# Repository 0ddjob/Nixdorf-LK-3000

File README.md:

# Nixdorf LK-3000
Information about the Nixdorf LK-3000 personal computer.<br>

The cartridges use the Mostek MK3870 CPU and MK3600 ROM.  The CPU contains its own ROM and RAM which can be [dumped](https://github.com/blackjetrock/dumper_m3780) thanks to the existence of a TEST pin!<br>

## Videos
- [Part 1: first look & disassembly](https://youtu.be/9jknng2B5vs)
- [Part 2: let's start hacking it](https://youtu.be/iGiR7imZPvE)
- [Part 3: Hello World!](https://youtu.be/sHEaltcKjgI)

## [Arduino Code](/Arduino/Hello_World/Hello_World.ino)
The first new software written for the LK-3000 in 40 years?!  Some test code to see how it works - replaced the cartridge connector with a 16-way pin header for easy wiring up to an Arduino.<br>

Check also the [July 1980 issue of Popular Electronics](/Documentation/Poptronics_July_1980.pdf) that describes how to re-use the LK-3000.

## [Dumping the MK3870 firmware](https://hackaday.com/tag/mk3870/)

## [Schematic](/LK3000_Schematics)
A schematic (KiCad 9) of the LK-3000.  The machine is essentially just a keyboard & display with the cartridges containing the processor, ROM and RAM (as appropriate).

## [Keyboard](/LK3000_Keyboard)
With the machine out of the case for testing/development with the Arduino, the original keyboard is not so easy to use.  So here's a simple replacement using 12mm tactile switches.

## [Arduino Cartridge](/LK3000_Arduino_Cartridge)
A design for a modern cartridge that uses the Arduino instead of the original Mostek microcontroller & ROM combination.

## [Breakout Cartridge](/LK3000_Breakout_Cartridge)
A design for a cartridge with breakout pin header so an external device can be connected for development/testing.

## [Prototyping Cartridge](/LK3000_Prototyping_Cartridge)
A design for a cartridge with prototyping area.

## [Logic Analyser Traces](/Saleae)
Signalling traces taken from the cartridge interface.  These were captured with the [Saleae logic analyser](https://www.saleae.com/) - their Logic 2 software is free to download & should open the file in "demo mode" (no need for the actual hardware).

## DL-1414 Display Modules
The LK-3000 uses four 4-character display modules (16 characters in total).  These parts are obsolete now but can still be found ... including in the LK-3000 obviously.<br>

There is an [Arduino library](https://github.com/marecl/HPDL1414) available to drive the modules directly.

## Cartridges
These are the cartridges that I'm aware of:
- LK-0280: Olympic Facts (Winter, Lake Placid 1980)
- LK-0680: Olympic Facts (Summer, Moscow 1980)
- LK-1001: Filing System
- LK-3050: English-Spanish
- LK-3060: English-French
- LK-3070: English-Italian
- LK-3080: English-German
- LK-3090: English-Swedish
- LK-3100: English-Polish
- LK-3110: English-Portuguese
- LK-3120: English-Russian
- LK-3130: English-Greek
- LK-3140: English-Arabic
- LK-3145: English-Arabic II
- LK-3160: English-Japanese
- LK-3200: English-Spanish-French-German-Italian-Greek
- LK-3500: Electronic Notepad
- LK-3900: Calculator

### LK-3050 Spanish Language 
Simple cartridge with processor (containing its own ROM & RAM) plus language ROM.

### LK-3500 Electronic Notepad
A more sophisticated cartridge with processor & rechargeable (NiCd) battery-backed RAM.

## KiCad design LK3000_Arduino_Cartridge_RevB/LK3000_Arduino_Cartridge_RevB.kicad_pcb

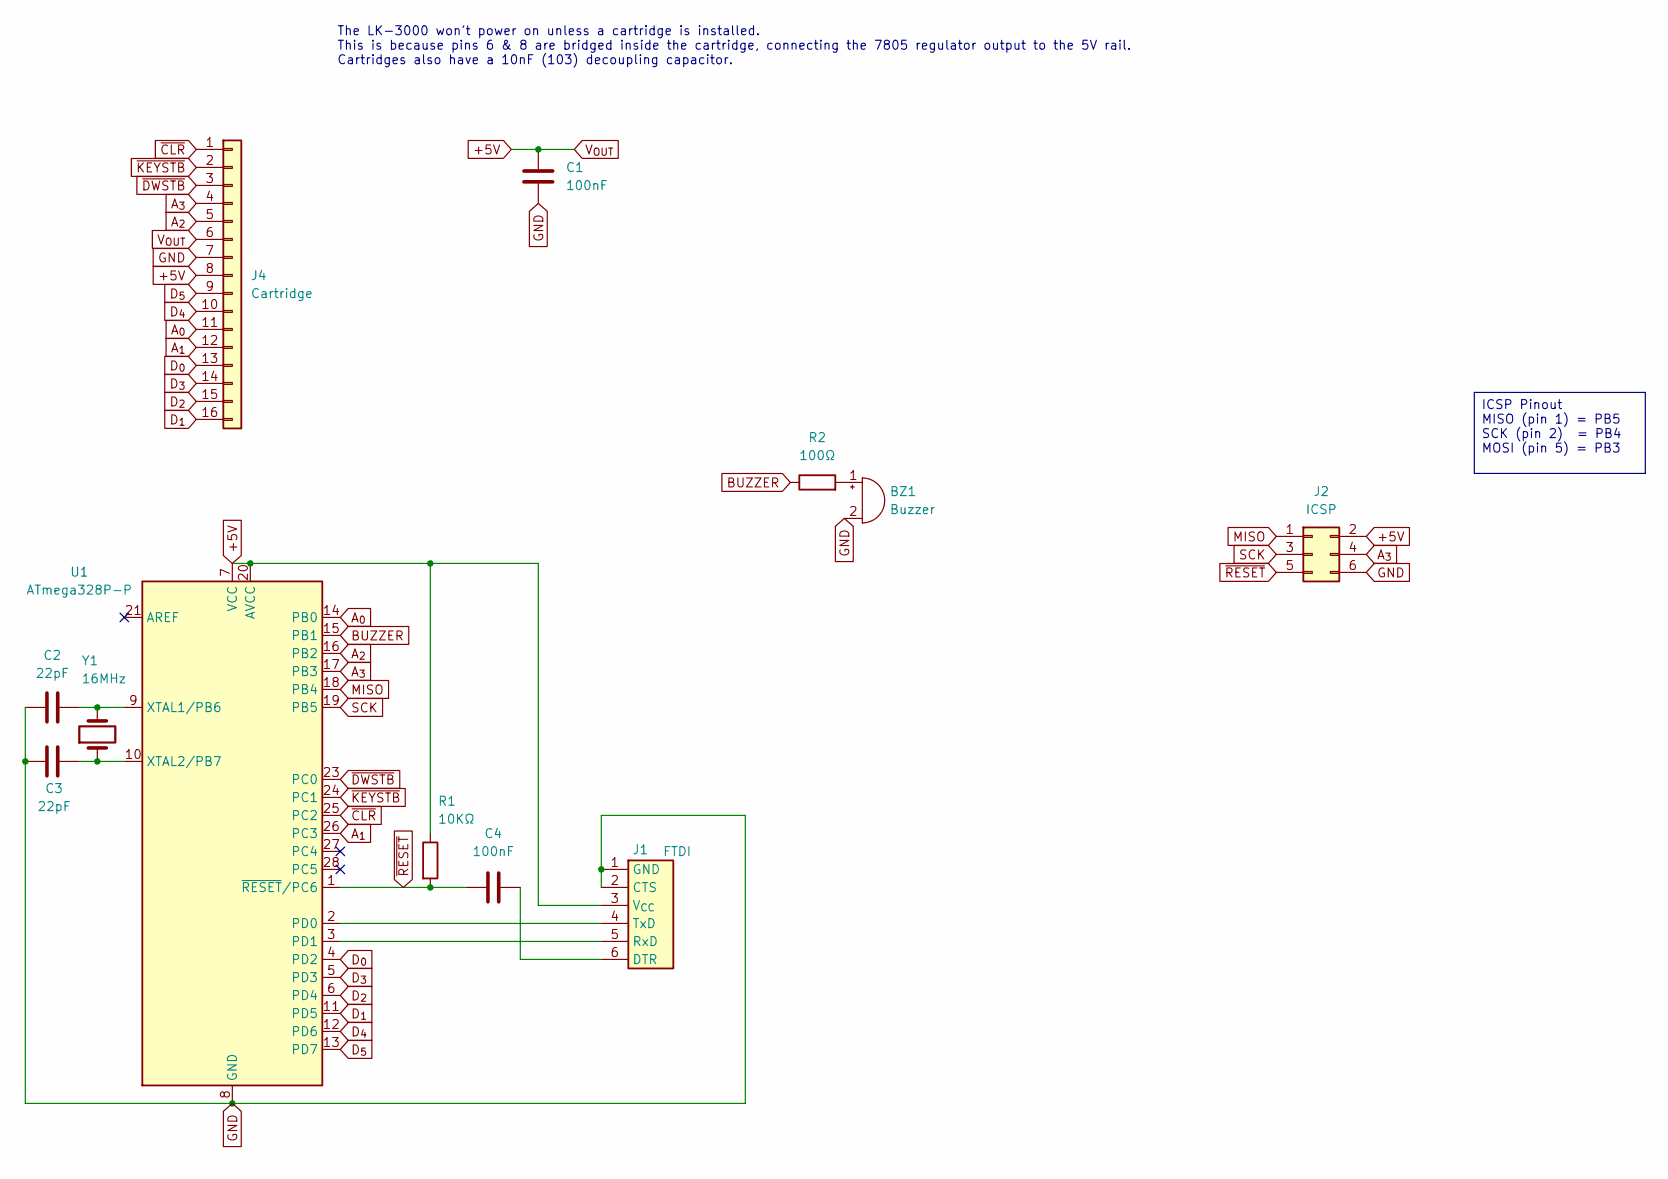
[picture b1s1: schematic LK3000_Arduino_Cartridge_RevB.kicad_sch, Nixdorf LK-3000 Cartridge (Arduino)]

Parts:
BZ1: Buzzer; Buzzer_15x7.5RM7.6
C1, C4: 100nF; C_Disc_D3.0mm_W2.0mm_P2.50mm
C2, C3: 22pF; C_Disc_D3.0mm_W2.0mm_P2.50mm
J1: FTDI; PinHeader_1x06_P2.54mm_Vertical
J2: ICSP; PinHeader_2x03_P2.54mm_Vertical
J4: Cartridge; LK-3000_Cartridge
R1: 10KΩ; R_Axial_DIN0207_L6.3mm_D2.5mm_P7.62mm_Horizontal
R2: 100Ω; R_Axial_DIN0207_L6.3mm_D2.5mm_P7.62mm_Horizontal
U1: ATmega328P-P; DIP-28_W7.62mm
Y1: 16MHz; Crystal_HC49-4H_Vertical

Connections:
+5V: C1.1, J1.3 (V_{CC}), J2.2, J4.6, J4.8, R1.1, U1.7 (VCC), U1.20 (AVCC)
A_{0}: J4.11, U1.14 (PB0)
A_{1}: J4.12, U1.26 (PC3)
A_{2}: J4.5, U1.16 (PB2)
A_{3}: J2.4, J4.4, U1.17 (PB3)
BUZZER: R2.1, U1.15 (PB1)
D_{0}: J4.13, U1.4 (PD2)
D_{1}: J4.16, U1.11 (PD5)
D_{2}: J4.15, U1.6 (PD4)
D_{3}: J4.14, U1.5 (PD3)
D_{4}: J4.10, U1.12 (PD6)
D_{5}: J4.9, U1.13 (PD7)
GND: BZ1.2 (-), C1.2, C2.1, C3.1, J1.1 (GND), J1.2 (CTS), J2.6, J4.7, U1.8 (GND), U1.22 (GND)
MISO: J2.1, U1.18 (PB4)
unnamed: BZ1.1 (+), R2.2
unnamed: C4.2, J1.6 (DTR)
unnamed: J1.5 (RxD), U1.3 (PD1)
unnamed: J1.4 (TxD), U1.2 (PD0)
unnamed: C2.2, U1.9 (XTAL1/PB6), Y1.2
unnamed: C3.2, U1.10 (XTAL2/PB7), Y1.1
SCK: J2.3, U1.19 (PB5)
~CLR: J4.1, U1.25 (PC2)
~DWSTB: J4.3, U1.23 (PC0)
~KEYSTB: J4.2, U1.24 (PC1)
~RESET: C4.1, J2.5, R1.2, U1.1 (~RESET/PC6)

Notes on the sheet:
The LK-3000 won't power on unless a cartridge is installed. This is because pins 6 & 8 are bridged inside the cartridge, connecting the 7805 regulator output to the 5V rail. Cartridges also have a 10nF (103) decoupling capacitor.
ICSP Pinout MISO (pin 1) = PB5 SCK (pin 2) = PB4 MOSI (pin 5) = PB3

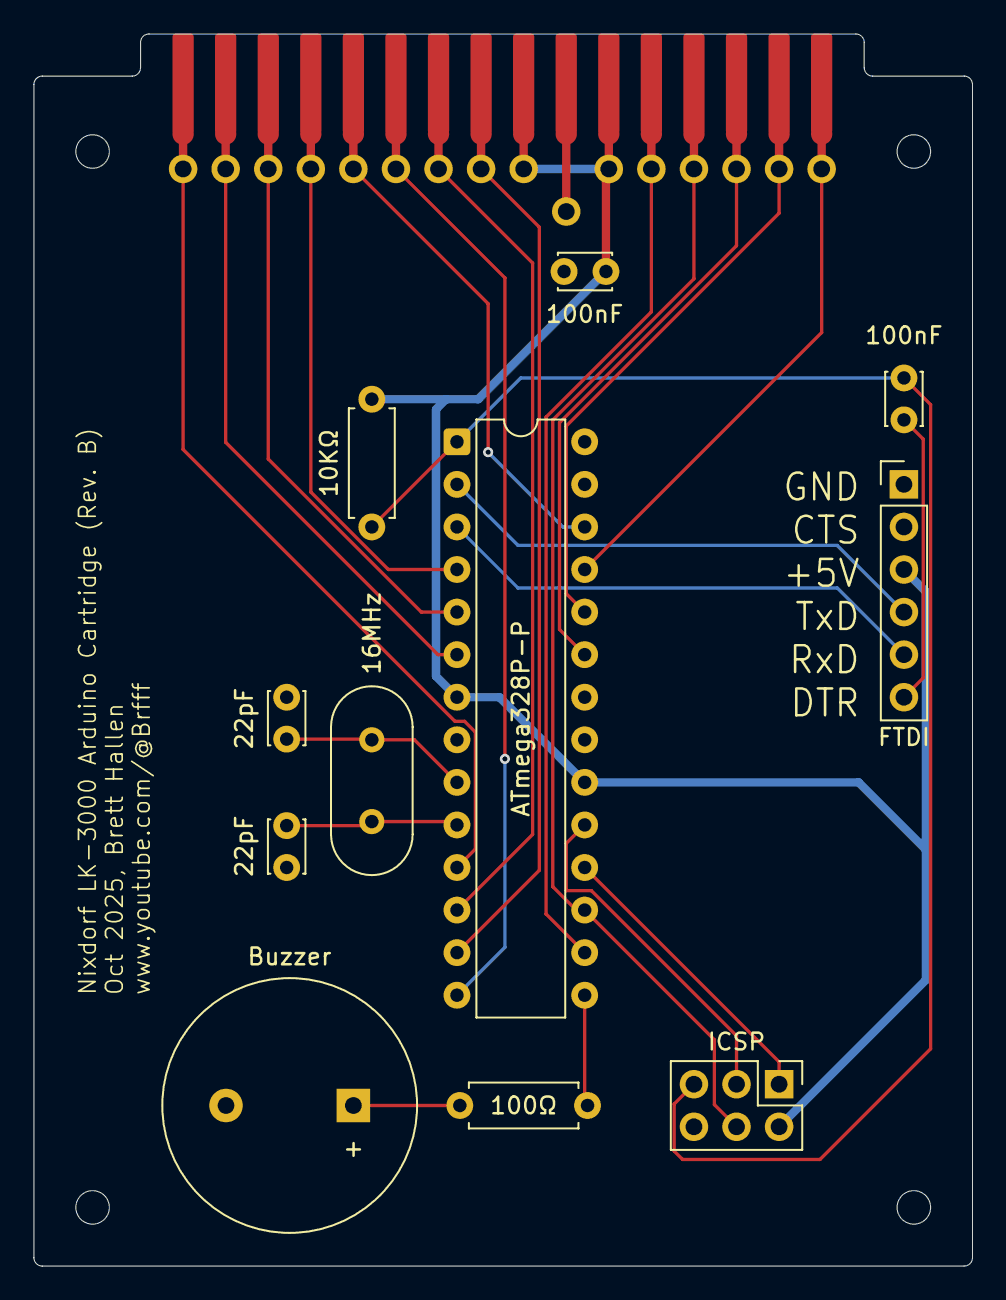
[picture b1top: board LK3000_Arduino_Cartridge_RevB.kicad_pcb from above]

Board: 2 copper layers, 56.0 x 73.5 mm, 12 parts (0 on the bottom side), 25 nets.

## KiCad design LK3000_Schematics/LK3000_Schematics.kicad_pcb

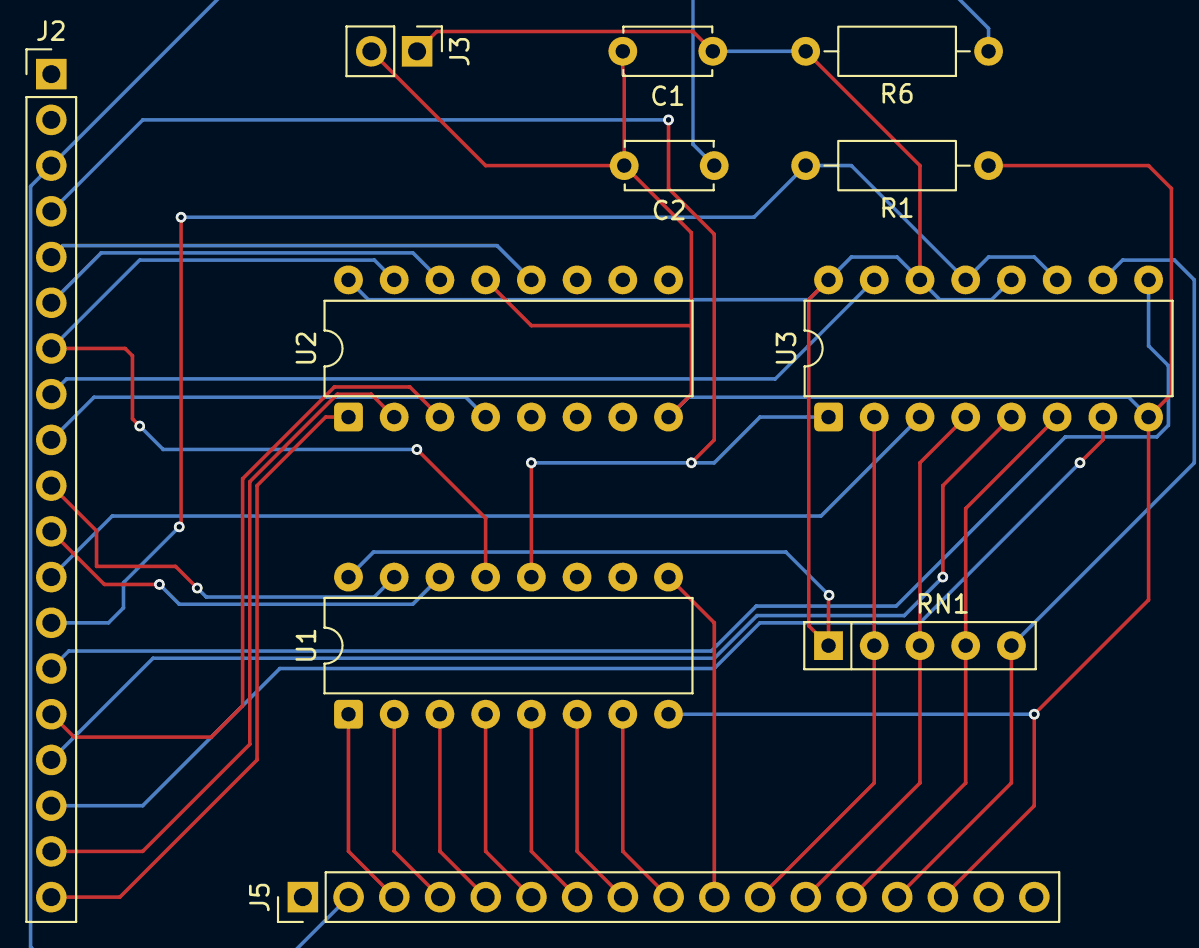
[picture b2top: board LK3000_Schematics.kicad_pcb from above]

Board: 2 copper layers, 11 parts (0 on the bottom side), 31 nets.

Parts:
C1: 10nF; C_Disc_D4.7mm_W2.5mm_P5.00mm
C2: 1µF; C_Disc_D4.7mm_W2.5mm_P5.00mm
J2: Keyboard-Display; PinHeader_1x19_P2.54mm_Vertical
J3: Power; PinHeader_1x02_P2.54mm_Vertical
J5: Keyboard; PinHeader_1x17_P2.54mm_Vertical
R1: 680Ω; R_Axial_DIN0207_L6.3mm_D2.5mm_P10.16mm_Horizontal
R6: 22KΩ; R_Axial_DIN0207_L6.3mm_D2.5mm_P10.16mm_Horizontal
RN1: 22KΩ; R_Array_SIP5
U1, U2: 74LS42; DIP-16_W7.62mm
U3: CD4503BE; DIP-16_W7.62mm

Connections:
+5V: C1.1, J3.1, R6.2, RN1.1 (common), U1.16 (VCC), U2.16 (VCC), U3.12 (D5), U3.14 (D6), U3.16 (VDD)
A_{0}: J2.10, U1.15 (A0)
A_{1}: J2.11, U1.14 (A1)
A_{2}: J2.7, U1.13 (A2), U2.15 (A0)
A_{3}: J2.6, U2.14 (A1)
COL1: J5.11, RN1.2 (R1), U3.2 (D1)
COL2: J5.12, RN1.3 (R2), U3.4 (D2)
COL3: J5.13, RN1.4 (R3), U3.6 (D3)
COL4: J5.14, RN1.5 (R4), U3.10 (D4)
D_{0}: J2.12, U3.3 (Q1)
D_{1}: J2.16, U3.5 (Q2)
D_{2}: J2.17, U3.7 (Q3)
D_{3}: J2.14, U3.9 (Q4)
D_{5}: J2.8, U3.15 (DIS_B)
D_{6}: J2.13, R1.2, U3.11 (Q5), U3.13 (Q6)
GND: C1.2, C2.2, J3.2, J5.15, R1.1, U1.8 (GND), U2.8 (GND), U2.13 (A2), U3.8 (VSS)
ROW1: J5.3, U1.1 (0)
ROW2: J5.4, U1.2 (1)
ROW3: J5.5, U1.3 (2)
ROW4: J5.6, U1.4 (3)
ROW5: J5.7, U1.5 (4)
ROW6: J5.8, U1.6 (5)
ROW7: J5.9, U1.7 (6)
ROW8: J5.10, U1.9 (7)
~CLR: C2.1, J2.3, J5.2, R6.1
~DWSTB: J2.5, U2.12 (A3)
~KEYSTB: J2.4, U1.12 (A3), U3.1 (DIS_A)
~WR_{1}: J2.9, U2.4 (3)
~WR_{2}: J2.15, U2.3 (2)
~WR_{3}: J2.18, U2.2 (1)
~WR_{4}: J2.19, U2.1 (0)

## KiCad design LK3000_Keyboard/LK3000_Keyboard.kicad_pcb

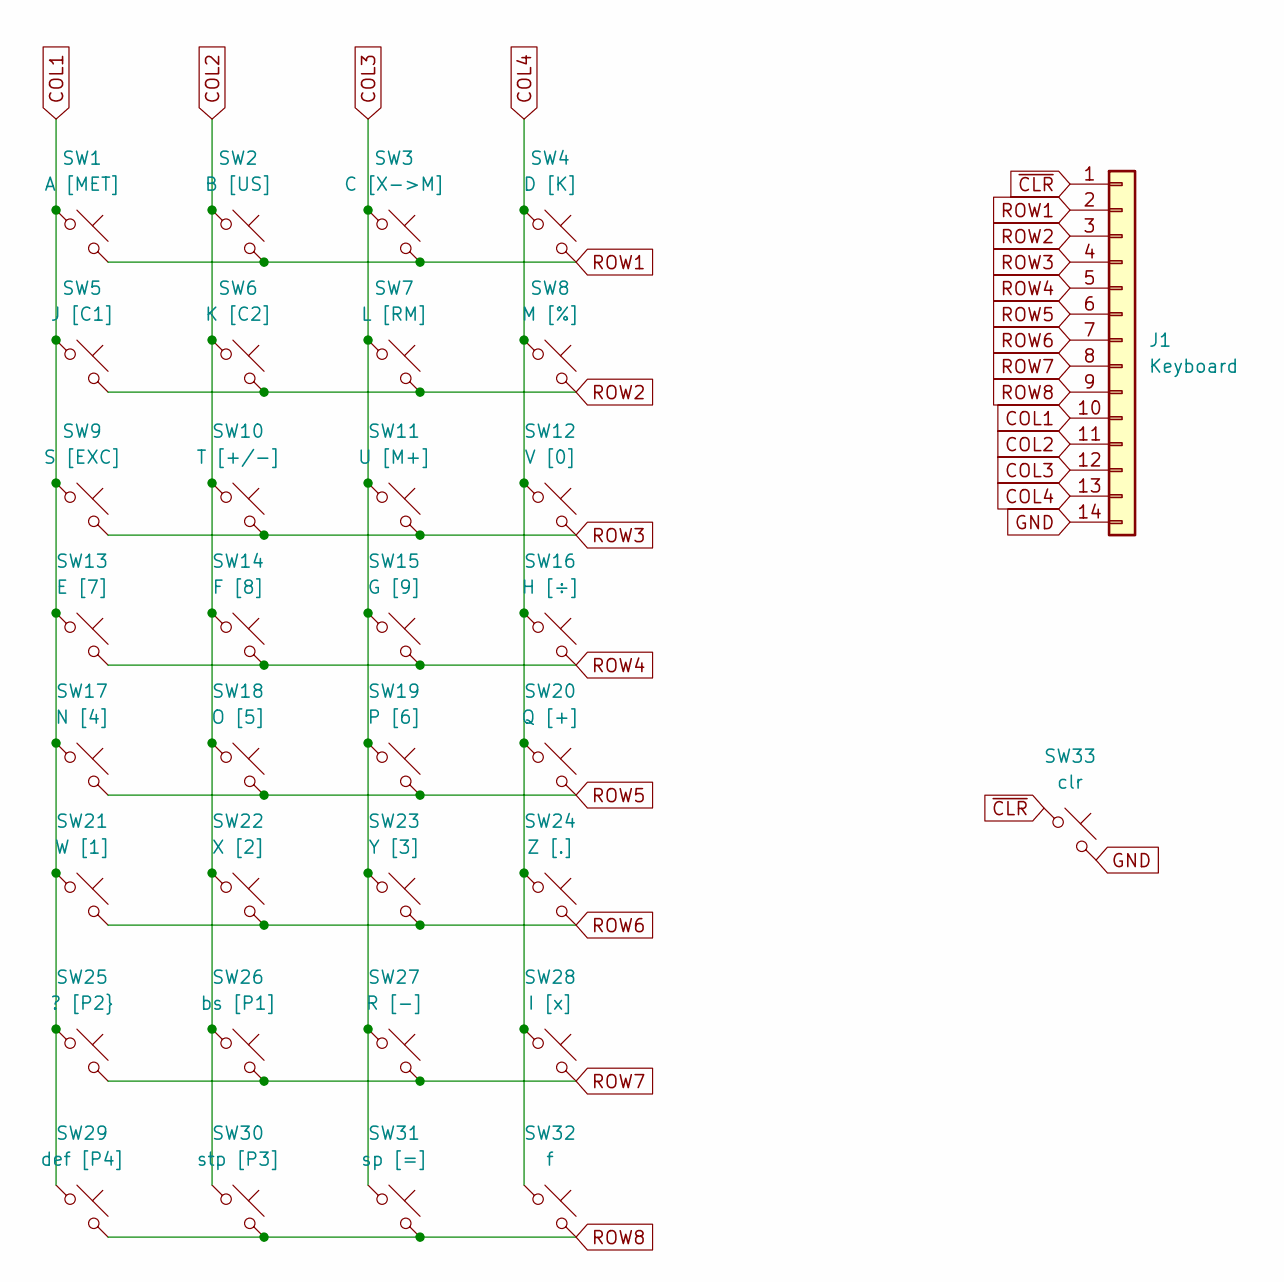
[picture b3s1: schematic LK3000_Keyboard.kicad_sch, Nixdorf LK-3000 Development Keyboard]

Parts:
J1: Keyboard; PinHeader_1x14_P2.54mm_Horizontal
SW1: A [MET]; SW_PUSH-12mm_Wuerth-430476085716
SW2: B [US]; SW_PUSH-12mm_Wuerth-430476085716
SW3: C [X->M]; SW_PUSH-12mm_Wuerth-430476085716
SW4: D [K]; SW_PUSH-12mm_Wuerth-430476085716
SW5: J [C1]; SW_PUSH-12mm_Wuerth-430476085716
SW6: K [C2]; SW_PUSH-12mm_Wuerth-430476085716
SW7: L [RM]; SW_PUSH-12mm_Wuerth-430476085716
SW8: M [%]; SW_PUSH-12mm_Wuerth-430476085716
SW9: S [EXC]; SW_PUSH-12mm_Wuerth-430476085716
SW10: T [+/-]; SW_PUSH-12mm_Wuerth-430476085716
SW11: U [M+]; SW_PUSH-12mm_Wuerth-430476085716
SW12: V [0]; SW_PUSH-12mm_Wuerth-430476085716
SW13: E [7]; SW_PUSH-12mm_Wuerth-430476085716
SW14: F [8]; SW_PUSH-12mm_Wuerth-430476085716
SW15: G [9]; SW_PUSH-12mm_Wuerth-430476085716
SW16: H [÷]; SW_PUSH-12mm_Wuerth-430476085716
SW17: N [4]; SW_PUSH-12mm_Wuerth-430476085716
SW18: O [5]; SW_PUSH-12mm_Wuerth-430476085716
SW19: P [6]; SW_PUSH-12mm_Wuerth-430476085716
SW20: Q [+]; SW_PUSH-12mm_Wuerth-430476085716
SW21: W [1]; SW_PUSH-12mm_Wuerth-430476085716
SW22: X [2]; SW_PUSH-12mm_Wuerth-430476085716
SW23: Y [3]; SW_PUSH-12mm_Wuerth-430476085716
SW24: Z [.]; SW_PUSH-12mm_Wuerth-430476085716
SW25: ? [P2}; SW_PUSH-12mm_Wuerth-430476085716
SW26: bs [P1]; SW_PUSH-12mm_Wuerth-430476085716
SW27: R [-]; SW_PUSH-12mm_Wuerth-430476085716
SW28: I [x]; SW_PUSH-12mm_Wuerth-430476085716
SW29: def [P4]; SW_PUSH-12mm_Wuerth-430476085716
SW30: stp [P3]; SW_PUSH-12mm_Wuerth-430476085716
SW31: sp [=]; SW_PUSH-12mm_Wuerth-430476085716
SW32: f; SW_PUSH-12mm_Wuerth-430476085716
SW33: clr; SW_PUSH-12mm_Wuerth-430476085716

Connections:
COL1: J1.10, SW1.1, SW5.1, SW9.1, SW13.1, SW17.1, SW21.1, SW25.1, SW29.1
COL2: J1.11, SW2.1, SW6.1, SW10.1, SW14.1, SW18.1, SW22.1, SW26.1, SW30.1
COL3: J1.12, SW3.1, SW7.1, SW11.1, SW15.1, SW19.1, SW23.1, SW27.1, SW31.1
COL4: J1.13, SW4.1, SW8.1, SW12.1, SW16.1, SW20.1, SW24.1, SW28.1, SW32.1
GND: J1.14, SW33.2
ROW1: J1.2, SW1.2, SW2.2, SW3.2, SW4.2
ROW2: J1.3, SW5.2, SW6.2, SW7.2, SW8.2
ROW3: J1.4, SW9.2, SW10.2, SW11.2, SW12.2
ROW4: J1.5, SW13.2, SW14.2, SW15.2, SW16.2
ROW5: J1.6, SW17.2, SW18.2, SW19.2, SW20.2
ROW6: J1.7, SW21.2, SW22.2, SW23.2, SW24.2
ROW7: J1.8, SW25.2, SW26.2, SW27.2, SW28.2
ROW8: J1.9, SW29.2, SW30.2, SW31.2, SW32.2
~CLR: J1.1, SW33.1

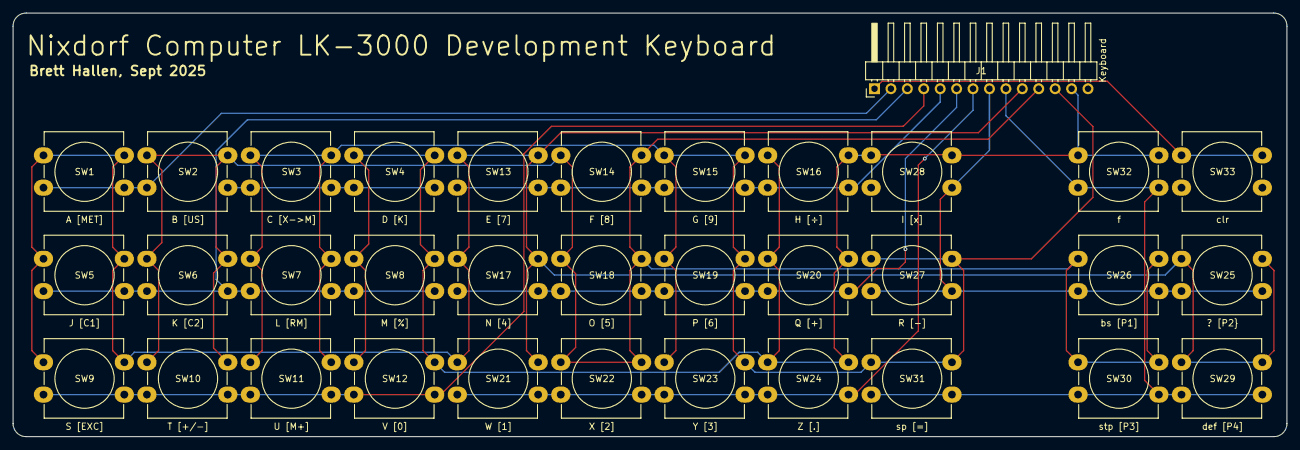
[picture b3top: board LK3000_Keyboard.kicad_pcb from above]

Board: 2 copper layers, 197.0 x 65.5 mm, 34 parts (0 on the bottom side), 14 nets.

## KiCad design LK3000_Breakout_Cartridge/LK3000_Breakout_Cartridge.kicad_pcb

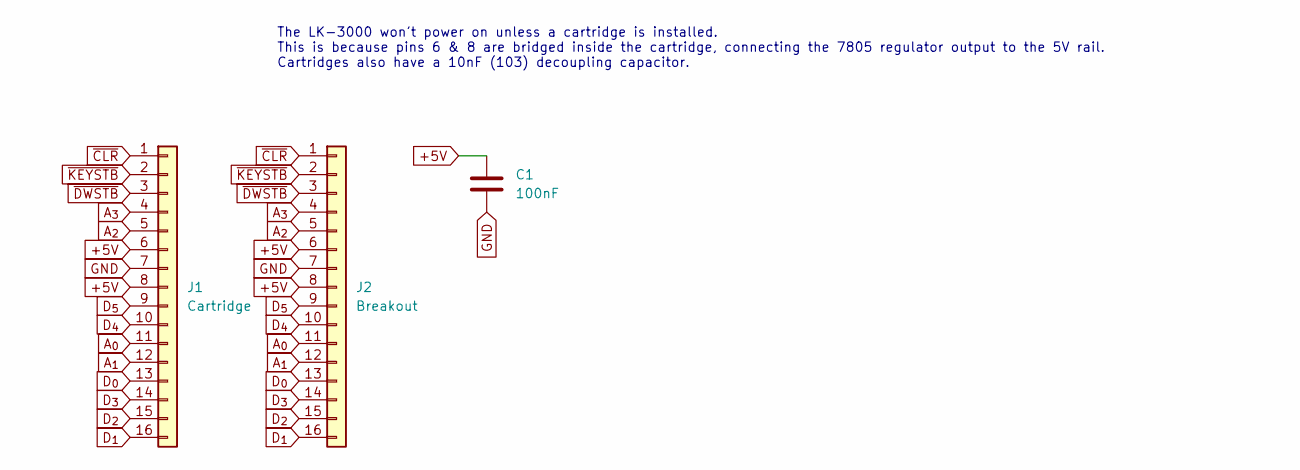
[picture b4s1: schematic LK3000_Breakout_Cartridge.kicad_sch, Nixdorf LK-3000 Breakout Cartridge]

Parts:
C1: 100nF; C_Disc_D3.0mm_W2.0mm_P2.50mm
J1: Cartridge; LK-3000_Cartridge
J2: Breakout; PinHeader_1x16_P2.54mm_Horizontal

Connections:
+5V: C1.1, J1.6, J1.8, J2.6, J2.8
A_{0}: J1.11, J2.11
A_{1}: J1.12, J2.12
A_{2}: J1.5, J2.5
A_{3}: J1.4, J2.4
D_{0}: J1.13, J2.13
D_{1}: J1.16, J2.16
D_{2}: J1.15, J2.15
D_{3}: J1.14, J2.14
D_{4}: J1.10, J2.10
D_{5}: J1.9, J2.9
GND: C1.2, J1.7, J2.7
~CLR: J1.1, J2.1
~DWSTB: J1.3, J2.3
~KEYSTB: J1.2, J2.2

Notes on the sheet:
The LK-3000 won't power on unless a cartridge is installed. This is because pins 6 & 8 are bridged inside the cartridge, connecting the 7805 regulator output to the 5V rail. Cartridges also have a 10nF (103) decoupling capacitor.

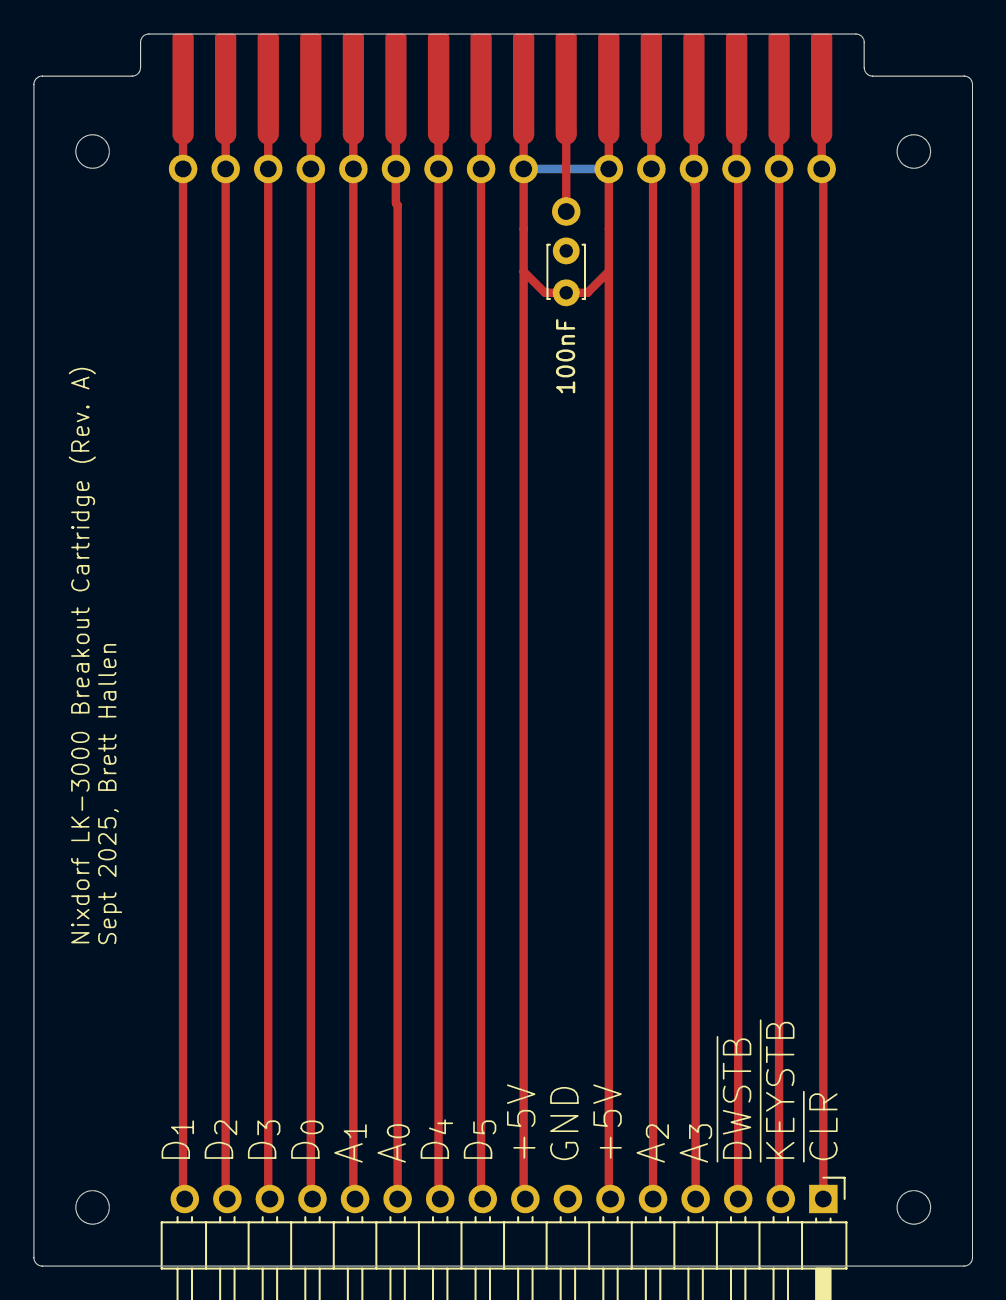
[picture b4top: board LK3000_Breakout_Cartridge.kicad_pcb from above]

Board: 2 copper layers, 56.0 x 73.5 mm, 3 parts (0 on the bottom side), 15 nets.

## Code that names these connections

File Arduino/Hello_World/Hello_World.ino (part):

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const int A_PINS[4] = {8, A3, 10, 11}; // A0 to A3 address bus
const int DWSTRB_PIN = A0; // Display write strobe (active low)
const int KEYSTRB_PIN = A1; // Keyboard strobe (active low)
const int CLR_PIN = A2; // Clear key input (active low)
const bool DEBUG_PRINTS = false; // Print debugging text to serial, slows everything down
const bool dispMode = false; // constant used for keyboard mode setting
const bool keybMode = true; // constant used for display mode setting
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
////////////////////////////////////////////
// LK-3000 Cartridge Port                 //
// Pin  1 = ~CLR button -> Arduino pin A2 //
// Pin  2 = ~KEYSTB -> Arduino pin A1     //
// Pin  3 = ~DWSTB -> Arduino pin A0      //
// Pin  4 = A3 -> Arduino pin 11          //
// Pin  5 = A2 -> Arduino pin 10          //
// Pin  6 = Vout                          //
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
  pinMode(DWSTRB_PIN, OUTPUT);
  pinMode(KEYSTRB_PIN, OUTPUT);
  pinMode(CLR_PIN, INPUT_PULLUP);
  setStrobe(keybMode); // keyboard strobe usually active unless outputting to display
}

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  bool keyPressed = false; // Track if any key is pressed in this scan

  // Check [f] key first (ROW8, COL4)
  digitalWrite(A_PINS[0], (7 & 0x01) ? HIGH : LOW); // ROW8 = 7
  digitalWrite(A_PINS[1], (7 & 0x02) ? HIGH : LOW);
  digitalWrite(A_PINS[2], (7 & 0x04) ? HIGH : LOW);
  setStrobe(keybMode);
  bool functionKeyPressed = (digitalRead(D_PINS[3]) == LOW); // COL4 via D3

  if (functionKeyPressed)
  {
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    // Pulse strobe
    setStrobe(keybMode);
    int cols = 0;
    if (digitalRead(D_PINS[0]) == LOW) cols |= 0x01; // COL1 via D0
    if (digitalRead(D_PINS[1]) == LOW) cols |= 0x02; // COL2 via D1
    if (digitalRead(D_PINS[2]) == LOW) cols |= 0x04; // COL3 via D2
    if (digitalRead(D_PINS[3]) == LOW) cols |= 0x08; // COL4 via D3

    if (cols && DEBUG_PRINTS)
    {
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
  // Check clear key - special handling
  unsigned long currentTime = millis();
  if (digitalRead(CLR_PIN) == LOW) 
  {
    keyPressed = true;
    if (currentTime - lastDebounceTime >= debounceDelay)
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
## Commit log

2025-09-22 initial cartridge designs
2025-09-22 Additional notes on schematic
2025-09-22 Additional images
2025-09-23 Updated schematic
2025-09-23 Logic analyser capture
2025-09-24 Created keyboard for development
2025-09-24 Test Arduino program
2025-09-24 Datasheets for the LK-3000
2025-09-24 Cartridge signalling trace with language module
2025-09-24 Relocate sketch
2025-09-25 Revised keyboard design to use 12mm tactile
2025-10-05 Schematic corrections
2025-10-06 Italian version of Popular Electronics article
2025-10-06 Minor corrections to schematic
2025-10-06 Drew PCB as per original to verify schematic
2025-10-06 Initial HELLO WORLD test sketch
2025-10-07 Tested display output
2025-10-07 Cartridge pinout for HELLO WORLD sketch
2025-10-07 Finalised schematic
2025-10-08 Added initial Arduino cartridge design
2025-10-08 Removed image background
2025-10-08 Additional text on PCB
2025-10-08 Started porting MicroChess
2025-10-14 Updated sketch
2025-10-18 Improvements to HELLO WORLD sketch
2025-10-19 Added shifted key handling
2025-10-29 Updated design
